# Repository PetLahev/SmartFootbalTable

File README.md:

# SmartFootbalTable
Arduino project for table football

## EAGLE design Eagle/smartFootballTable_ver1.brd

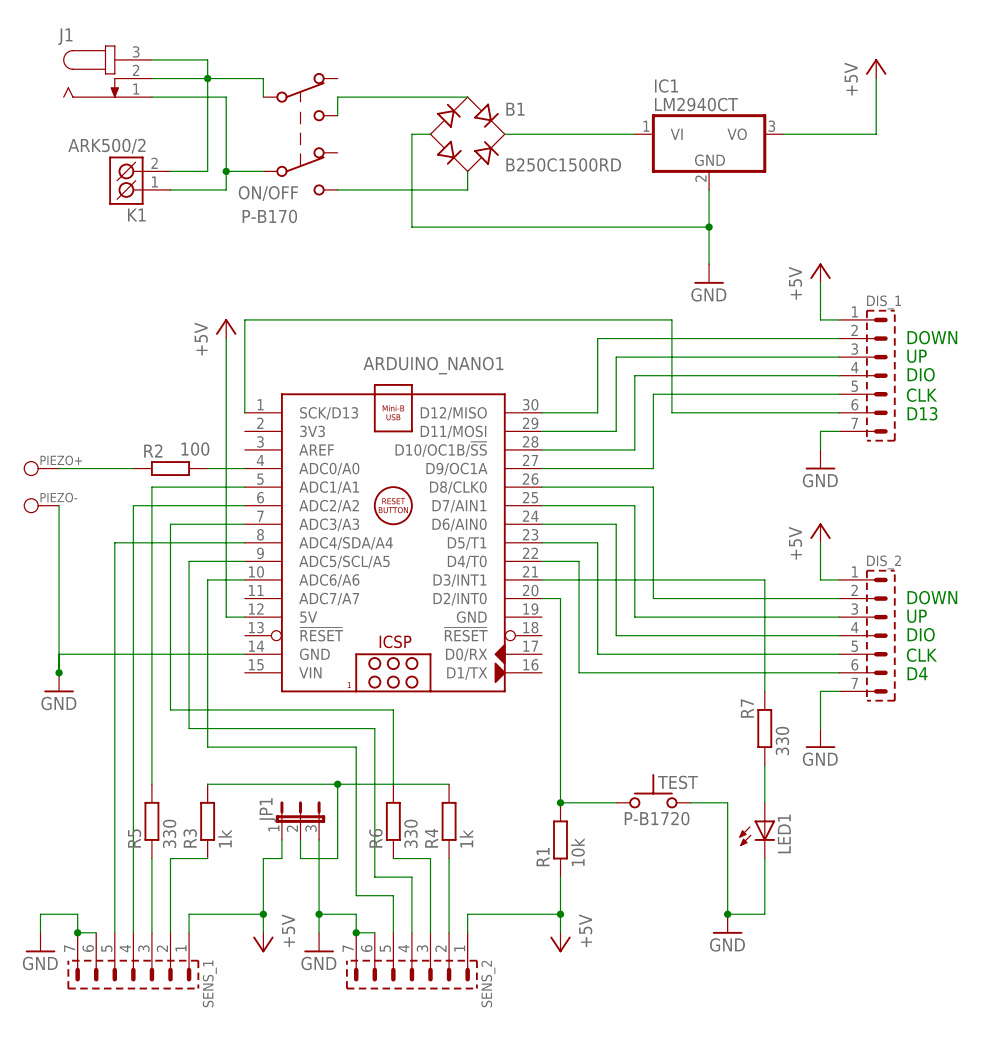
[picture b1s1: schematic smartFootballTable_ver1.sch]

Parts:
ARDUINO_NANO1: ARDUINO_NANO
B1: B250C1500RD; RB1A
DIS_1, DIS_2: PSH02-07W
IC1: LM2940CT; TO220H; MPN LM2940CT-5.0/NOPB
J1: JACK-PLUG1; SPC4078
JP1: JP2W
K1: ARK500/2
LED1: LED5MM
ON/OFF: P-B170
PIEZO+: PAD_1+; PAD_1
PIEZO-: PAD_1-; PAD_1
R1: 10k; 0204/7
R2: 100; 0204/7
R3, R4: 1k; 0204/7
R5, R6, R7: 330; 0204/7
SENS_1, SENS_2: PSH02-07W
TEST: P-B1720

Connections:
+5V: ARDUINO_NANO1.12 (5V), DIS_1.1, DIS_2.1, IC1.3 (VO), JP1.1, R1.1, SENS_1.1, SENS_2.1
A0: ARDUINO_NANO1.4 (ADC0/A0), R2.2
A1: ARDUINO_NANO1.5 (ADC1/A1), R5.2
A2: ARDUINO_NANO1.6 (ADC2/A2), SENS_1.4
A3: ARDUINO_NANO1.7 (ADC3/A3), R6.2
A4: ARDUINO_NANO1.9 (ADC5/SCL/A5), SENS_2.4
A5: ARDUINO_NANO1.8 (ADC4/SDA/A4), SENS_1.5
A6: ARDUINO_NANO1.10 (ADC6/A6), SENS_2.5
D2: ARDUINO_NANO1.20 (D2/INT0), R1.2, TEST.1
D3: ARDUINO_NANO1.21 (D3/INT1), R7.2
D4: ARDUINO_NANO1.22 (D4/T0), DIS_2.6
D11: ARDUINO_NANO1.29 (D11/MOSI), DIS_1.3
D12: ARDUINO_NANO1.30 (D12/MISO), DIS_1.2
D13: ARDUINO_NANO1.1 (SCK/D13), DIS_1.6
DIS1_CLK: ARDUINO_NANO1.27 (D9/OC1A), DIS_1.5
DIS1_DIO: ARDUINO_NANO1.28 (D10/OC1B/!SS), DIS_1.4
DIS2_CLK: ARDUINO_NANO1.23 (D5/T1), DIS_2.5
DIS2_DIO: ARDUINO_NANO1.24 (D6/AIN0), DIS_2.4
DIS2_DOWN: ARDUINO_NANO1.26 (D8/CLK0), DIS_2.2
DIS2_UP: ARDUINO_NANO1.25 (D7/AIN1), DIS_2.3
GND: ARDUINO_NANO1.14 (GND), ARDUINO_NANO1.19 (GND), B1.-, DIS_1.7, DIS_2.7, IC1.2 (GND), JP1.3, LED1.K (C), PIEZO-.1, SENS_1.6, SENS_1.7, SENS_2.6, SENS_2.7, TEST.2
unnamed: J1.1, K1.1 (K1), ON/OFF.6 (X2)
unnamed: B1.AC2, ON/OFF.5 (R2)
unnamed: B1.AC1, ON/OFF.2 (R1)
unnamed: J1.2, J1.3, K1.2 (K2), ON/OFF.3 (X1)
unnamed: PIEZO+.1, R2.1
unnamed: R3.1, SENS_1.2
unnamed: R4.1, SENS_2.2
unnamed: R5.1, SENS_1.3
unnamed: R6.1, SENS_2.3
unnamed: LED1.A, R7.1
unnamed: JP1.2, R3.2, R4.2
VCC: B1.+, IC1.1 (VI)
VIN: ARDUINO_NANO1.15 (VIN)

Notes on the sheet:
CLK
DIO
DOWN
D13

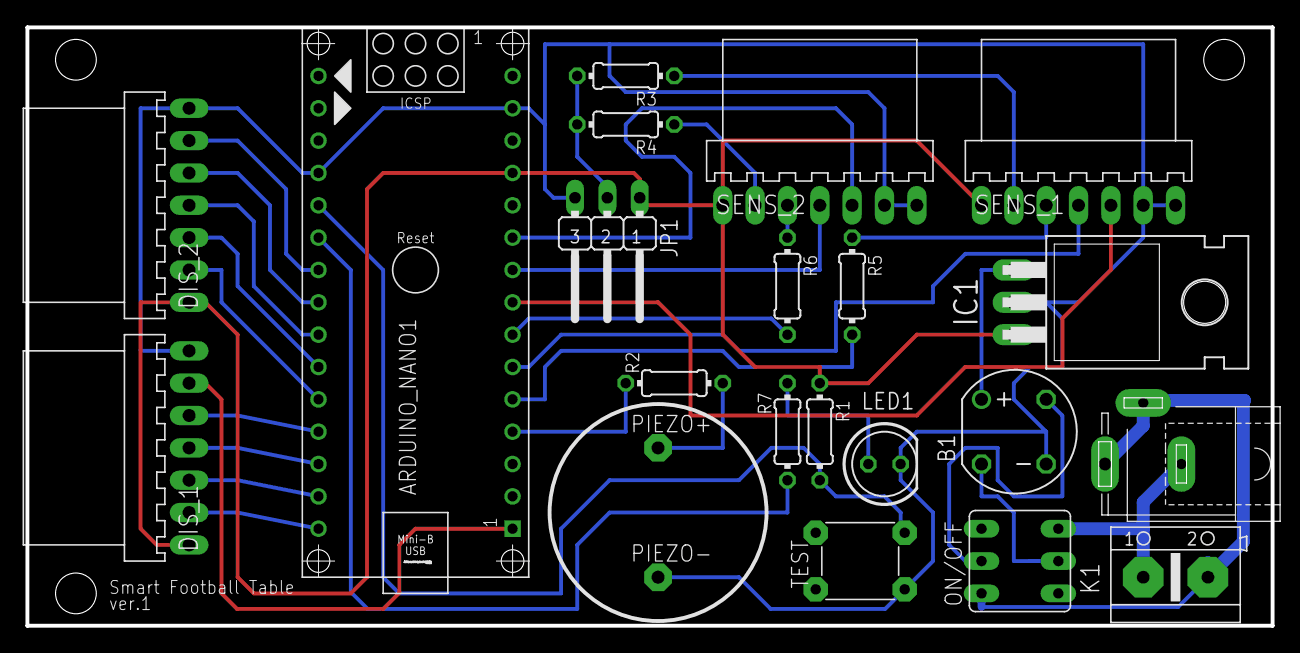
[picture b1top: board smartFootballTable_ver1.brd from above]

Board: 2 copper layers, 97.8 x 47.0 mm, 22 parts (0 on the bottom side), 33 nets.

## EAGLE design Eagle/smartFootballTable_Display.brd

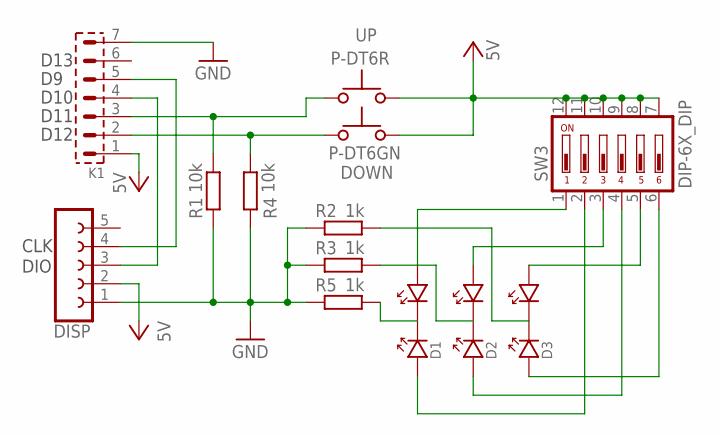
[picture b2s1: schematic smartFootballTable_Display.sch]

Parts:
D1, D2, D3: LED_DUO_3; LED_3-DUO
DISP: FE05W
DOWN: P-DT6GN; P-DTE6
K1: PSH02-07W
R1, R4: 10k; 0204/7
R2, R3, R5: 1k; 0204/7
SW3: DIP-6X_DIP; DIP-6X
UP: P-DT6R; P-DTE6

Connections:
CLK: DISP.4, K1.5
DIO: DISP.3, K1.4
GND: DISP.1, K1.7, R1.1, R2.1, R3.1, R4.1, R5.1
unnamed: K1.3, R1.2, UP.1
unnamed: DOWN.1, K1.2, R4.2
unnamed: D1.A2, SW3.1
unnamed: D2.A1, SW3.4
unnamed: D2.A2, SW3.3
unnamed: D3.A2, SW3.5
unnamed: D3.A1, SW3.6
unnamed: D1.A1, SW3.2
unnamed: D3.K, R2.2
unnamed: D2.K, R3.2
unnamed: D1.K, R5.2
VCC: DISP.2, DOWN.2, K1.1, SW3.7, SW3.8, SW3.9, SW3.10, SW3.11, SW3.12, UP.2

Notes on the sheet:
DIO
CLK
D12
D11
D10
D13

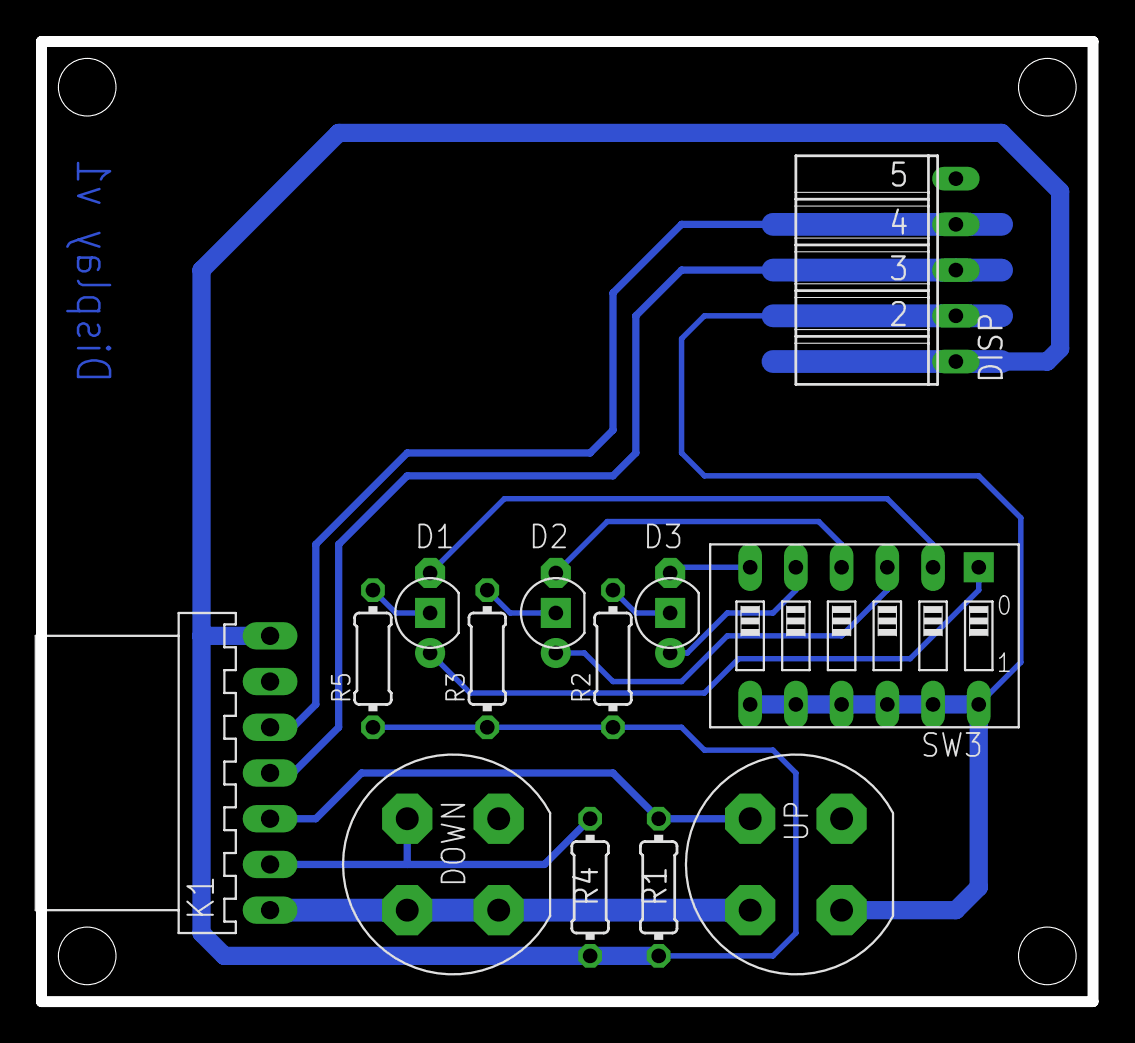
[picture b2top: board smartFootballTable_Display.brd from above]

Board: 2 copper layers, 58.4 x 53.3 mm, 13 parts (0 on the bottom side), 15 nets.

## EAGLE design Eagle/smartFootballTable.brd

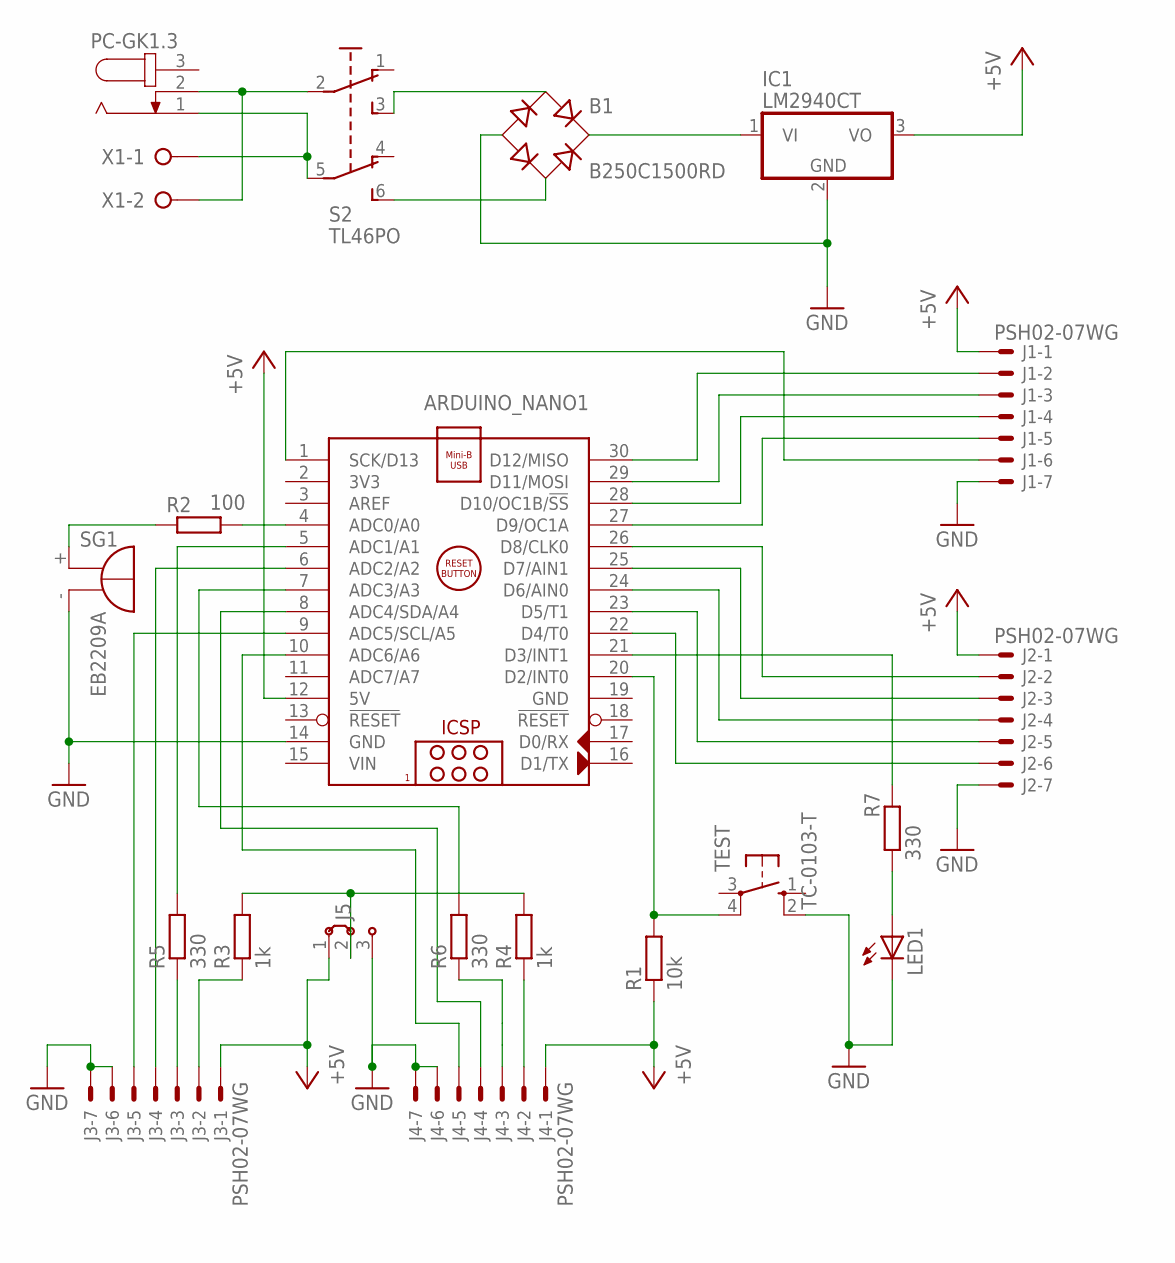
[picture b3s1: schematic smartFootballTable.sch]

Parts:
ARDUINO_NANO1: ARDUINO_NANO
B1: B250C1500RD; RB1A
IC1: LM2940CT; TO220H; MPN LM2940CT-5.0/NOPB
J1, J2, J3, J4: PSH02-07WG; 70553-07
J5: J2X2MM; 04C
LED1: LED5MM
PC-GK1.3: JACK-PLUG0; SPC4077
R1: 10k; 0204/7
R2: 100; 0204/7
R3, R4: 1k; 0204/7
R5, R6, R7: 330; 0204/7
S2: TL46PO; TL4XPO
SG1: EB2209A
TEST: TC-0103-T; B3F-40XX; MPN B3F-4000 BY OMZ
X1: W237-02P; W237-132

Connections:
+5V: ARDUINO_NANO1.12 (5V), IC1.3 (VO), J1.1, J2.1, J3.1, J4.1, J5.1, R1.1
A0: ARDUINO_NANO1.4 (ADC0/A0), R2.2
A1: ARDUINO_NANO1.5 (ADC1/A1), R5.2
A2: ARDUINO_NANO1.6 (ADC2/A2), J3.4
A3: ARDUINO_NANO1.7 (ADC3/A3), R6.2
A4: ARDUINO_NANO1.8 (ADC4/SDA/A4), J4.4
A5: ARDUINO_NANO1.9 (ADC5/SCL/A5), J3.5
A6: ARDUINO_NANO1.10 (ADC6/A6), J4.5
D2: ARDUINO_NANO1.20 (D2/INT0), R1.2, TEST.4 (P1)
D3: ARDUINO_NANO1.21 (D3/INT1), R7.2
D4: ARDUINO_NANO1.22 (D4/T0), J2.6
D5: ARDUINO_NANO1.23 (D5/T1), J2.5
D6: ARDUINO_NANO1.24 (D6/AIN0), J2.4
D7: ARDUINO_NANO1.25 (D7/AIN1), J2.3
D8: ARDUINO_NANO1.26 (D8/CLK0), J2.2
D9: ARDUINO_NANO1.27 (D9/OC1A), J1.5
D10: ARDUINO_NANO1.28 (D10/OC1B/!SS), J1.4
D11: ARDUINO_NANO1.29 (D11/MOSI), J1.3
D12: ARDUINO_NANO1.30 (D12/MISO), J1.2
D13: ARDUINO_NANO1.1 (SCK/D13), J1.6
GND: ARDUINO_NANO1.14 (GND), ARDUINO_NANO1.19 (GND), B1.-, IC1.2 (GND), J1.7, J2.7, J3.6, J3.7, J4.6, J4.7, J5.3, LED1.K (C), SG1.-, TEST.2 (S1)
unnamed: B1.+, IC1.1 (VI)
unnamed: B1.AC2, S2.6 (S1)
unnamed: B1.AC1, S2.3 (S)
unnamed: R2.1, SG1.+
unnamed: PC-GK1.3.1, S2.5 (P1), X1.1
unnamed: PC-GK1.3.2, S2.2, X1.2
unnamed: J3.2, R3.1
unnamed: J4.2, R4.1
unnamed: J3.3, R5.1
unnamed: J4.3, R6.1
unnamed: LED1.A, R7.1
unnamed: J5.2, R3.2, R4.2
VIN: ARDUINO_NANO1.15 (VIN)

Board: 2 copper layers, 21 parts (0 on the bottom side), 33 nets, no tracks yet.

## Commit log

2017-04-25 Eagle scheme and board
2017-04-28 PlatformIO settings
    Trying the PlatformIO editor and its settings
2017-05-03 Created ver1 for the board
2017-05-03 The fabricated board
2017-05-14 Updated board with latest changes after soldering
2017-05-14 Added display scheme and board
2017-05-16 Added another version of the display scheme and board
    Plus the Eagle files
2017-05-17 Made changes for the display board before fabrication
2017-05-28 Added pin description and started with PlatformIO
2017-07-02 Added special debaouncer logic for football buttons. Added Score class (ideally this should be moved outside the main.cpp)
2017-07-02 Added constants class Having problem with reseting the Arduino board when using Serial.print. I assume there is a problem with the pointers I'm using. Also display2 is not working properly
2017-07-03 Fixed bug with memory (wrong size of data arrays in the Socer class) Changed the Constants header to use const inseatd of def
2017-07-03 Added GOAl constant and tried to rename the Constant file
2017-07-04 Added globals for TM1637 display so it can be called from everywhere
2017-07-04 Created score class
2017-07-04 Added some display and tone when a game ends
2017-07-04 Added new testButton class for running hardware tests

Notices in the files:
parts and their libraries:
Copyright (C) PaJa 2001-2014
Copyright (C) PaJa 2011-2014
